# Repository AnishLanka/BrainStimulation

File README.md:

# BrainStimulation — Prototype Demo 2 / PCB Package Rev C

By Pythagoras Carayannopoulos, Peter Zhao and Anish Lanka.
Presentation: [`docs/Prototype_Demo_2.pdf`](docs/Prototype_Demo_2.pdf)

Start with `docs/RevC_Release/READ_ME_FIRST.txt` and `docs/RevC_Release/Integration_Guide.html`.
Upload each board's manufacturing ZIP to JLCPCB as a separate bare PCB design.
Do not upload the complete release archive as one PCB.

## TEAM

| Person | Responsibilities |
|--------|------------------|
| Pythagoras Carayannopoulos (Pyth) | Boost, Howland Pump circuit design, soldering, testing |
| Anish Lanka | Rail Splitter, Buck-Boost, Howland Pump schematic and PCB, soldering, testing |
| Peter Zhao | Signal Generator, firmware (ESP32-S3 controller, RP2040 DDS, web and Android apps), testing |

## SYSTEM OVERVIEW

The signal generator sets the shape of the stimulation current. The power path
provides the energy and voltage to push it. The two paths meet at the Howland,
which turns the voltage command into a current.

```
POWER PATH   Battery ──► Buck-Boost ──► Isolated 12 V ──► Boost ──► Rail Splitter
             2.8–3.7 V   steady 3.3 V   new isolated      79.7 V    ±39.85 V about MID
                                        domain                           │ ±40 V
                                                                         ▼
                                                                     Howland ──► External load
                                                                         ▲      electrodes; 2–5 kΩ on bench
                                                                         │ ±3.3 V command
SIGNAL PATH  Pico 2 W ──► ISOW7741 ──────► DAC8830 ──────► OPA2192
             samples      isolates SPI     code→0–3.3 V    bipolar ±3.3 V
                          and power
```

Compared with the Stim the Brim design we built on (~60 V boost, ±30 V rails),
ours uses ~80 V / ±40 V so firmware can limit output to ±30 V without clipping
from rail saturation.

## REPOSITORY LAYOUT

Every board folder follows the same pattern:

```
<Board>/
  *_JLCPCB.zip / *_fabrication.zip   Gerbers — upload this to JLCPCB
  Release_DRC.json                   Rev C release DRC report
  kicad/
    Anish_Work/                      Anish's KiCad files for this board
    Peter_Work/                      Peter's KiCad files for this board
    Pyth_Work/                       Pyth's KiCad files for this board
```

Open the `.kicad_pro` inside a `*_Work/` folder and keep that folder together —
project libraries are referenced relatively. Empty work folders hold a `.gitkeep`.

```
boards/
  Boost/                 Boost_79V7_Prototype_JLCPCB.zip, Boost_FINAL_ASSEMBLY_BOM.csv
    kicad/Pyth_Work/       Boost_Electrical_Draft.kicad_pro (Rev C project)
                           Boost_Convertor_Circuit_Pyth.kicad_sch (working changes)
  Buck_Boost/            BuckBoost_RevB_fabrication.zip
    kicad/Pyth_Work/       BuckBoost_RevB.kicad_pro (Rev C project)
                           BuckBoost_RevBPythWork.zip (working copy of project)
  Rail_Splitter/         RailSplitter_Prototype_JLCPCB.zip, RailSplitter_FINAL_ASSEMBLY_BOM.csv
    kicad/Anish_Work/      RailSplitter_Electrical_Draft.kicad_pro (Rev C project)
                           AmplifierCircuit_MYCHANGES.kicad_sch (working changes)
  Howland_Pump/          HowlandPump_JLCPCB.zip, Howland_Read_Only_Calculation.json
    kicad/Anish_Work/      HowlandPump-AnishWork.kicad_pro (current, Oct 2)
                           older_versions/ (FINAL + Backout, Sep 30)
  Signal_Generator/      SignalGen_Prototype_RevC_JLCPCB.zip, FIRMWARE_COMPATIBILITY.txt
    kicad/Peter_Work/      SignalGen_Electrical_Draft.kicad_pro (Rev C project)
  Shared/                Boards not assigned to a single owner
    Channel_ADC_Interface_RevC/   kicad/Peter_Work/Channel_ADC_Interface_RevC.kicad_pro
    Channel_Monitor_C1/           kicad/Peter_Work/Channel_Monitor_C1.kicad_pro
    Monitor_Power_C1/             kicad/Peter_Work/Monitor_Power_C1.kicad_pro
    Shared_Power_RevC/            kicad/Peter_Work/Shared_Power_Adapter_RevC.kicad_pro
docs/
  Prototype_Demo_2.pdf              Prototype Demo 2 presentation
  Firmware.md                       Firmware guide (commands, protocol, pins, build)
  RevC_Release/                     System-level release documents:
                                    READ_ME_FIRST.txt, Integration_Guide.html,
                                    Wiring_Map.json, Release_Checks.json, SHA256SUMS.json,
                                    Existing_Power_Review, Legacy_Power_Assembly/
firmware/                         Peter Zhao
  ESP32_S3_Brainstim_FW/            ESP32-S3 main controller (ESP-IDF 5.4): BLE control,
                                    4-channel FSM, OLED, battery/ADC; web/ BLE test UI;
                                    mobile/ Capacitor Android app; tests/ host simulations
  RP2040_DDS_FW/                    DDS daughter card, now Pico 2 W + DAC8830 (Pico SDK
                                    2.2.0; folder name is historical): DMA-paced SPI DAC
                                    streaming, waveform tables, I2C slave
releases/
  StimPrototype_Prototype_Package_RevC.zip   Original Rev C archive, unmodified
```

The files from the release archive have been distributed into the folders above.
Paths inside `Integration_Guide.html`, `Release_Checks.json` and `SHA256SUMS.json`
refer to the original archive layout — use the zip in `releases/` when you need
those links and checksums to line up.

## BOARDS AND TEST STATUS (Prototype Demo 2)

| Board | Owner | Soldered | Bench result |
|-------|-------|----------|--------------|
| Buck-Boost RevB | Anish | Yes | **Pass** — 3.3036 V out (target 3.3 V). Battery not yet on hand. |
| Boost 79.7 V | Pyth | Yes | **Pass** — 12 V in, ~79.5 V out (scope average). |
| Rail Splitter | Anish | Yes | **Open** — could not bring input to full voltage; op amp possibly damaged. Split appeared even. |
| Howland Pump | Pyth (design) / Anish (schematic + PCB) | Yes | **Fail** — measured 96 V peak-to-peak; LTspice simulation works. Not yet debugged. |
| Signal Generator RevC | Peter | Yes | Fixes applied (below); expected ±3.3 V output. |
| Monitor Power C1 | Shared | — | New in Rev C — one local supply per channel. |
| Channel Monitor C1 | Shared | — | New in Rev C — external sensing/relay board. |
| Channel ADC Interface RevC | Shared | — | New in Rev C — isolated simultaneous I/V sampler per channel. |
| Shared Power RevC | Shared | — | New in Rev C — OPTIONAL regulated 5 V bench adapter (not a raw-cell supply). |

## DESIGN NOTES

**Buck-Boost (TPS63001).** Steps the 2.8–3.7 V battery up or down to a steady
3.3 V. The battery starts near 3.7 V and decays toward 2.8 V.

**Boost (LM5155).** 12 V in → 79.7 V out. Vout = Vin ÷ (1 − D), so the switch is on
about 85 % of the time.
- Feedback set to 79.7 V: R1 = 787 kΩ, R2 = 10 kΩ.
- Parts that see 80 V were up-rated: Q1 100 V → 150 V; D1 100 V → 200 V;
  top feedback resistor 0603 (~75 V max) → 1206 (200 V);
  C5 22 µF / 100 V → 100 µF / 160 V.

**Rail Splitter (OPA455).** Splits 79.7 V into HV_TOP = +39.85 V,
MID = 0 V, HV_BOTTOM = −39.85 V (relative to MID). MID is the reference for the
Howland and the isolated signal stage. Matched 100 kΩ 0.1 % divider, output
resistor for stability, added bulk and rail-to-rail filter capacitors, and a
+40 / MID / −40 connector to other boards.

**Howland Pump (OPA462).** Circuit designed by Pyth; schematic and PCB by Anish. Designed for up to ±5 mA. Rails are ±40 V
rather than ±30 V to avoid saturation near the voltage limit. The 2 kΩ Rload1
placeholder is DNP; use external 2–5 kΩ dummy loads. A read-only calculation in
the release flags a resistor-ratio mismatch; the proposed R11 20k → 24k
correction is **not** applied. Confirm fitted values before wiring.

**Signal Generator (Pico 2 W → ISOW7741 → DAC8830 → OPA2192).**
Vout = 2 × Vdac − 3.3 V, so DAC 0 / 1.65 / 3.3 V → −3.3 / 0 / +3.3 V.
- The DAC8830 output (~6.25 kΩ source) was driving a 10 kΩ load directly;
  the OPA2192 now buffers it.
- Footprint changed from the 6-pin DAC8411 to the 8-pin DAC8830.
- At power-up the DAC outputs code 0 = −3.3 V (full negative). **Firmware must set
  mid-scale first.**
- Firmware is now modular: TypeScript front-end web app, C back-end, Student and
  Teacher views.

## FIRMWARE

Written by Peter Zhao.

Full documentation: [`docs/Firmware.md`](docs/Firmware.md) — architecture, BLE
commands, I2C protocol, pin maps, safety sequencing, build/test and TODOs.

Two projects that must be updated together — they share the 15-byte GET_STATUS v2
I2C protocol. Detailed handoff: `firmware/ESP32_S3_Brainstim_FW/docs/phase1.md`.
Keep both folders side by side: the host tests find the RP2040 code at
`../RP2040_DDS_FW`.

- **RP2040:** `cmake -S . -B build-phase1 -G Ninja -DCMAKE_BUILD_TYPE=Release`, then
  `cmake --build build-phase1` (needs `PICO_SDK_PATH`, `PICO_TOOLCHAIN_PATH`).
- **ESP32-S3:** `idf.py build` with ESP-IDF 5.4.
- **Host tests:** `node tests/run_phase1.mjs` from `ESP32_S3_Brainstim_FW/`
  (needs Node and Clang with wasm-ld).
- Build output (`build/`, `build-*/`, `sdkconfig.old`, `node_modules/`) is
  git-ignored. Regenerate locally.

Not yet flashed or validated on hardware. The ESP32 refuses stimulation until HV
GPIO assignments and polarity are confirmed in `main/gpio_pins.h`.

## ORDER SETTINGS

2 layers; FR4; nominal 0.4 mm; 1 oz copper; ENIG; green mask; white silk;
tented vias. Follow the per-board README. These files do not order assembled
PCBs or purchase components. Support these thin boards during assembly.

## CHECKS

`Release_Checks.json` in the release archive records a fresh DRC (KiCad 10.0.6,
2026-10-17) on every packaged native project; reports are in `Release_Validation/`
and file hashes in `SHA256SUMS.json`. DRC/ERC validate file connectivity and
geometry, not powered performance.

## OPEN ISSUES

1. Howland: 96 V p-p on the bench despite a working simulation — investigate.
2. Rail Splitter: replace/verify the op amp and retest at full 79.7 V input.
3. `boards/Rail_Splitter/kicad/Anish_Work/AmplifierCircuit_MYCHANGES.kicad_sch` lists C1–C4 as
   **10 V** capacitors, but they sit on an 80 V / ±40 V rail (the presented design
   uses 100 V parts). Check which values were actually fitted.
4. Battery, charger and protection not yet selected; runtime unknown.
5. Do not parallel separate 3.3 V outputs. The two primary supply connectors on
   each SignalGen board are internally tied together.
6. Firmware/hardware DAC mismatch — **resolved 2026-10-30**: the next build targets
   the **DAC8830 on a Pico 2 W**, and `firmware/RP2040_DDS_FW` was retargeted
   accordingly (16-bit mode-0 frames, PIO CS framing, Rev C pin map, EN/FLT fault
   bit). Still open: compile with the Pico SDK, re-run the host tests, scope the
   DAC interface, and decide how the board's second channel is driven
   (`boards/Signal_Generator/FIRMWARE_COMPATIBILITY.txt`, `docs/Firmware.md`).

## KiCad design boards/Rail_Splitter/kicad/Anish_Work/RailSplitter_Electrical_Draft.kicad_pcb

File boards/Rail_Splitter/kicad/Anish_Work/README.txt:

RAIL SPLITTER - ENGINEERING BENCH PROTOTYPE

Open RailSplitter_Electrical_Draft.kicad_pro in KiCad10. The schematic, PCB and local libraries
are included. The routed PCB matches the schematic and passes the checks in
PCB_DRC.json / PCB_Validation.json. Read PCB_Draft_Notes.txt for mechanics,
pinout and layout decisions, Draft_Review.txt for electrical assumptions, and
Fabrication_Order_Notes.txt for the0.4 mm bare-board order. The top-level upload
archive is RailSplitter_Prototype_JLCPCB.zip. The hardware still requires assembly and bench testing.

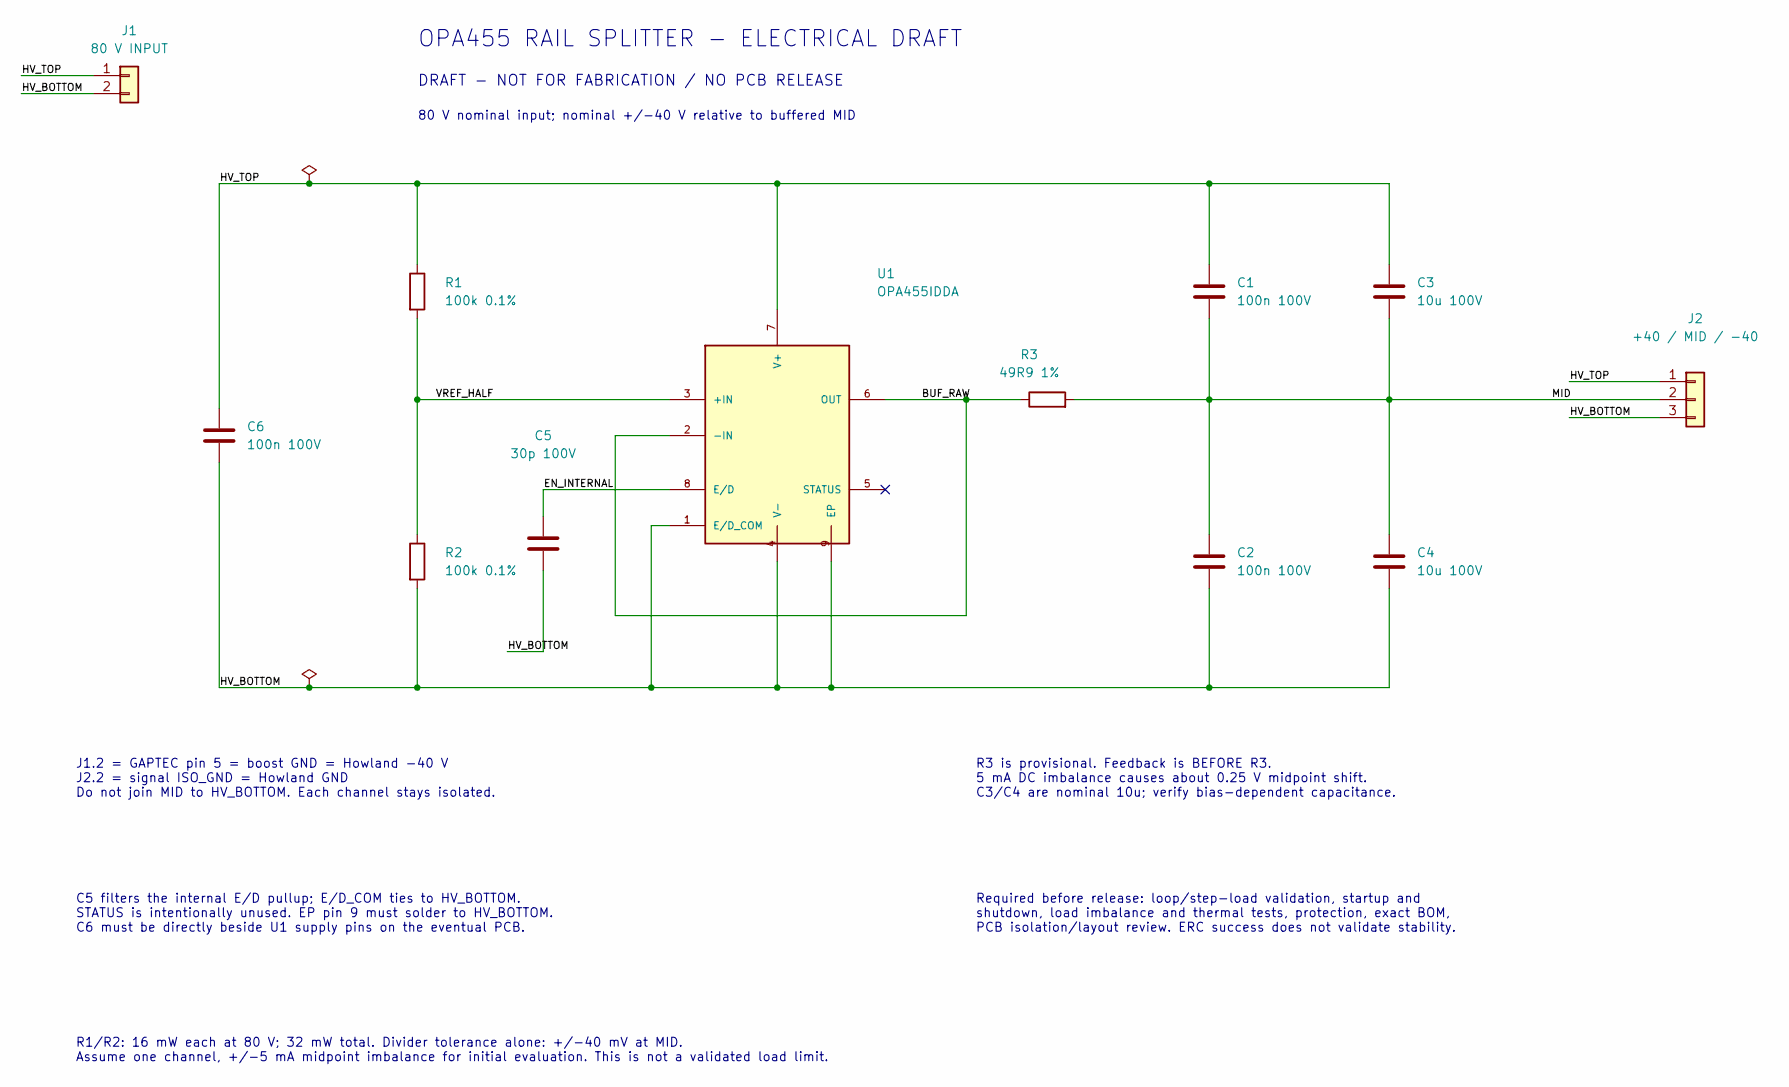
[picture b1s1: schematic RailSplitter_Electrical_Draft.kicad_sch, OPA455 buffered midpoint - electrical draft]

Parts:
C1, C2, C6: 100n 100V; C0805; MPN C2012X7R2A104K125AA
C3, C4: 10u 100V; C1210; MPN GRM32EC72A106KE05K
C5: 30p 100V; C0603
J1: 80 V INPUT; J2
J2: +40 / MID / -40; J3
R1, R2: 100k 0.1%; R0805; Rating 0.125W minimum; 100V minimum working vo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
R3: 49R9 1%; R0805; Rating 0.125W minimum
U1: OPA455IDDA; OPA455_DDA0008J; MPN OPA455IDDA

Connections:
/BUF_RAW: R3.1, U1.2 (-IN), U1.6 (OUT)
/EN_INTERNAL: C5.1, U1.8 (E/D)
/HV_BOTTOM: C2.2, C4.2, C5.2, C6.2, J1.2, J2.3, R2.2, U1.1 (E/D_COM), U1.4 (V-), U1.9 (EP)
/HV_TOP: C1.1, C3.1, C6.1, J1.1, J2.1, R1.1, U1.7 (V+)
/MID: C1.2, C2.1, C3.2, C4.1, J2.2, R3.2
/VREF_HALF: R1.2, R2.1, U1.3 (+IN)

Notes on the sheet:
OPA455 RAIL SPLITTER - ELECTRICAL DRAFT
DRAFT - NOT FOR FABRICATION / NO PCB RELEASE
80 V nominal input; nominal +/-40 V relative to buffered MID
J1.2 = GAPTEC pin 5 = boost GND = Howland -40 V J2.2 = signal ISO_GND = Howland GND Do not join MID to HV_BOTTOM. Each channel stays isolated.
R3 is provisional. Feedback is BEFORE R3. 5 mA DC imbalance causes about 0.25 V midpoint shift. C3/C4 are nominal 10u; verify bias-dependent capacitance.
C5 filters the internal E/D pullup; E/D_COM ties to HV_BOTTOM. STATUS is intentionally unused. EP pin 9 must solder to HV_BOTTOM. C6 must be directly beside U1 supply pins on the eventual PCB.
Required before release: loop/step-load validation, startup and shutdown, load imbalance and thermal tests, protection, exact BOM, PCB isolation/layout review. ERC success does not validate stability.
R1/R2: 16 mW each at 80 V; 32 mW total. Divider tolerance alone: +/-40 mV at MID. Assume one channel, +/-5 mA midpoint imbalance for initial evaluation. This is not a validated load limit.

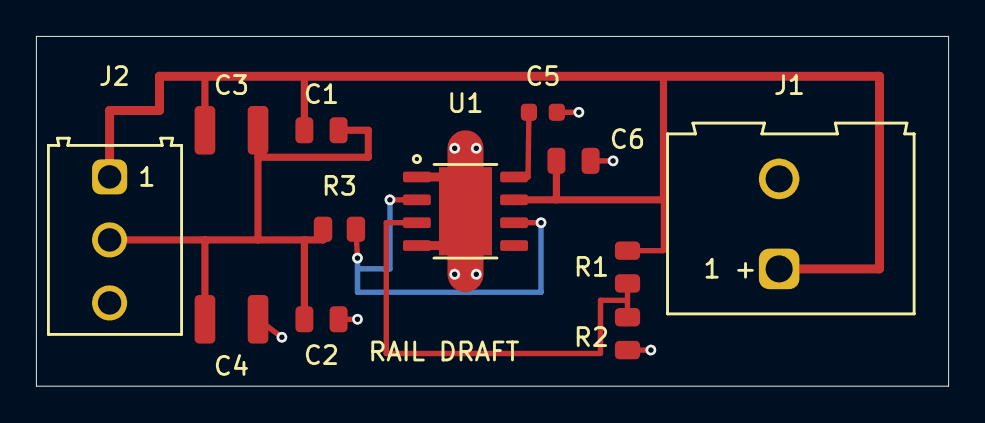
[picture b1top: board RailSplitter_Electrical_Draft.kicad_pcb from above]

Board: 2 copper layers, 50.7 x 19.4 mm, 12 parts (0 on the bottom side), 6 nets.

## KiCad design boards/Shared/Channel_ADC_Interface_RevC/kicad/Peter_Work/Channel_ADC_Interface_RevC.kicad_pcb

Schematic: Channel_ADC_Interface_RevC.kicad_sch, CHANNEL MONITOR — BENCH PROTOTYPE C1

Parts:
C201, C207: 1.2n; C_0805_2012Metric; MPN C0805C122F5GACTU
C202, C204, C208, C210: 1n; C_0805_2012Metric; MPN C0805C102F5GACTU
C203, C209: 6.8n; C_0805_2012Metric; MPN C0805C682F5GACTU
C205, C211: 8.2n; C_0805_2012Metric; MPN C0805C822F5GACTU
C206, C212, C219, C221, C223, C224, C225, C226, C227, C228: 100n; C_0805_2012Metric; MPN C0805C104K4RACTU
C213, C216, C220, C222: 22u; C_1210_3225Metric; MPN GRM32ER71C226KEA8L
J201: HOST_CONTROL_TELEMETRY; PinHeader_1x08_P2.54mm_Vertical; MPN TSW-108-07-G-S
J202: CORE_ADC_CONTROL_LINK; PinHeader_2x07_P2.54mm_Vertical; MPN TSW-107-07-G-D
R201, R202, R209, R210: 2k; R_0805_2012Metric; MPN TNPW08052K00BEEA
R203, R211: 470R; R_0805_2012Metric; MPN TNPW0805470RBEEA
R204, R212: 1.47k; R_0805_2012Metric; MPN TNPW08051K47BEEA
R205, R206, R213, R214: 604R; R_0805_2012Metric; MPN TNPW0805604RBEEA
R207, R208, R215, R216: 10R; R_0805_2012Metric; MPN TNPW080510R0BEEA
R221, R222, R223, R229, R230, R231, R232, R233, R234, R235, R236, R237: 10k; R_0805_2012Metric; MPN TNPW080510K0BEEA
R224, R225, R226, R227, R228: 33R; R_0805_2012Metric; MPN TNPW080533R0BEEA
R238, R239: 0.1R; R_0805_2012Metric; MPN WSL0805R1000FEA
U201, U202: OPA2320; SOIC-8_3.9x4.9mm_P1.27mm; MPN OPA2320AID
U204: ADS8353; TSSOP-16_4.4x5mm_P0.65mm; MPN ADS8353IPW
U205: ISO7741F; SOIC-16W_7.5x10.3mm_P1.27mm; MPN ISO7741FDWR
U206: ISO7721F; SOIC-16W_7.5x10.3mm_P1.27mm; MPN ISO7721FDWR
U207: Raspberry Pi Pico RP2040; RaspberryPi_Pico_Common_THT; MPN SC0915
U208: SN74LVC1G08; SOT-23-5; MPN SN74LVC1G08DBVR
U209: SN74LVC2G17; SOT-23-6; MPN SN74LVC2G17DBVR

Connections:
/ADC_CS_N: R221.2, R224.2, U204.11 (~CS)
/ADC_REF_A: R238.1, U204.3 (REFIO_A)
/ADC_REF_B: R239.1, U204.6 (REFIO_B)
/ADC_SCLK: R222.1, R225.2, U204.12 (SCLK)
/ADC_SDI: R223.1, R226.2, U204.10 (SDI)
/ADC_SDO_A: R227.1, U204.13 (SDO_A)
/ADC_SDO_B: R228.1, U204.14 (SDO_B)
/ARM_EDGE: J202.9, U205.13 (OUTB)
/FAULT_CLEAR_N: J202.11, R237.1, U205.11 (IND), U209.1 (1A)
/HEARTBEAT: J202.10, U205.12 (OUTC)
/HOST_3V3: C223.1, C225.1, J201.1, R234.2, U205.1 (VCC1), U205.7 (EN1), U206.3 (VCC1)
/HOST_ARM: J201.4, R230.1, U205.4 (INB)
/HOST_FAULT_OK: J201.6, R233.1, U205.6 (OUTD)
/HOST_GND: C223.2, C225.2, J201.2, R229.2, R230.2, R231.2, R233.2, U205.2 (GND1), U205.8 (GND1), U206.1 (GND1), U206.7 (GND1)
/HOST_HB: J201.5, R231.1, U205.5 (INC)
/HOST_RUN: J201.3, R229.1, U205.3 (INA)
/HOST_UART_RX: J201.8, U206.4 (OUTA)
/HOST_UART_TX: J201.7, R234.1, U206.5 (INB)
/INHIBITED: J202.12, U209.3 (2A)
/ISOLATED_HOST_RUN: R232.1, U205.14 (OUTA), U208.1 (A)
/I_ADC_N: C205.2, R208.2, U204.2 (AINM_A)
/I_ADC_P: C205.1, R207.2, U204.1 (AINP_A)
/I_F1A: C201.1, R203.2, R204.1
/I_F1B: C202.1, R204.2, U201.3 (INA+)
/I_F2A: C203.1, R205.2, R206.1
/I_F2B: C204.1, R206.2, U201.5 (INB+)
/I_HALF: R201.2, R202.1, R203.1
/I_LP1: C201.2, R205.1, U201.1 (OUTA), U201.2 (INA-)
/I_LP2: C203.2, R207.1, U201.6 (INB-), U201.7 (OUTB)
/I_MON: J202.5, R201.1
/LOCAL_READY: R236.1, U207.10 (GP7), U208.2 (B)
/MID_CH_GND: C202.2, C204.2, C206.2, C208.2, C210.2, C212.2, C213.2, C216.2, C219.2, C220.2, C221.2, C222.2, C224.2, C226.2, C227.2, C228.2, J202.2, J202.4, R202.2, R208.1, R210.2, R216.1, R222.2, R223.2, R232.2, R236.2, R237.2, U201.4 (V-), U202.4 (V-), U204.4 (REFGND_A), U204.5 (REFGND_B), U204.15 (GND), U205.9 (GND2), U205.15 (GND2), U206.9 (GND2), U206.16 (GND2), U207.3 (GND), U207.8 (GND), U207.13 (GND), U207.18 (GND), U207.23 (GND), U207.28 (GND), U207.33 (AGND), U207.38 (GND), U208.3 (GND), U209.2 (GND)
/P3V3_CH: C224.1, C227.1, J202.3, U205.10 (EN2), U205.16 (VCC2), U208.5 (VCC)
/P5_CH: C206.1, C212.1, C219.1, C220.1, J202.1, U201.8 (V+), U202.8 (V+), U204.16 (AVDD), U207.39 (VSYS)
/PICO_3V3: C221.1, C222.1, C226.1, C228.1, R221.1, R235.2, U204.9 (DVDD), U206.14 (VCC2), U207.36 (3V3_OUT), U209.5 (VCC)
/PICO_ADC_CS_N: R224.1, U207.4 (GP2)
/PICO_ADC_SCLK: R225.1, U207.5 (GP3)
/PICO_ADC_SDI: R226.1, U207.6 (GP4)
/PICO_ADC_SDO_A: R227.2, U207.7 (GP5)
/PICO_ADC_SDO_B: R228.2, U207.9 (GP6)
/PICO_FAULT_OK: U207.11 (GP8), U209.6 (1Y)
/PICO_INHIBITED: U207.12 (GP9), U209.4 (2Y)
/PICO_UART_RX: U206.12 (OUTB), U207.2 (GP1)
/PICO_UART_TX: R235.1, U206.13 (INA), U207.1 (GP0)
/REF_A_CAP: C213.1, R238.2
/REF_B_CAP: C216.1, R239.2
/RUN_REQUEST: J202.8, U208.4 (Y)
/V_ADC_N: C211.2, R216.2, U204.7 (AINM_B)
/V_ADC_P: C211.1, R215.2, U204.8 (AINP_B)
/V_F1A: C207.1, R211.2, R212.1
/V_F1B: C208.1, R212.2, U202.3 (INA+)
/V_F2A: C209.1, R213.2, R214.1
/V_F2B: C210.1, R214.2, U202.5 (INB+)
/V_HALF: R209.2, R210.1, R211.1
/V_LP1: C207.2, R213.1, U202.1 (OUTA), U202.2 (INA-)
/V_LP2: C209.2, R215.1, U202.6 (INB-), U202.7 (OUTB)
/V_MON: J202.6, R209.1

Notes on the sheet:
CHANNEL ADC / ISOLATED LOCAL SAMPLER — REV C DUMMY-LOAD BENCH PROTOTYPE
0.5 Hz–40 kHz measurement target. ADS8353 + matched analogue filters + local Pico PIO/DMA + isolated UART and controls.
MID_CH_GND = channel core MID_CH; isolated from HOST_GND. Never parallel PICO_3V3 regulator output with core P3V3_CH.
External supplies through J201/J202 (flags are source declarations, not regulators):
OPA2320AID
TNPW08052K00BEEA
TNPW0805470RBEEA
TNPW08051K47BEEA
C0805C122F5GACTU
C0805C102F5GACTU
TNPW0805604RBEEA
C0805C682F5GACTU
TNPW080510R0BEEA
C0805C822F5GACTU
C0805C104K4RACTU
GRM32ER71C226KEA8L
ADS8353IPW
TNPW080510K0BEEA
TNPW080533R0BEEA
ISO7741FDWR
ISO7721FDWR
SC0915
SN74LVC1G08DBVR
SN74LVC2G17DBVR
TSW-108-07-G-S
TSW-107-07-G-D
WSL0805R1000FEA

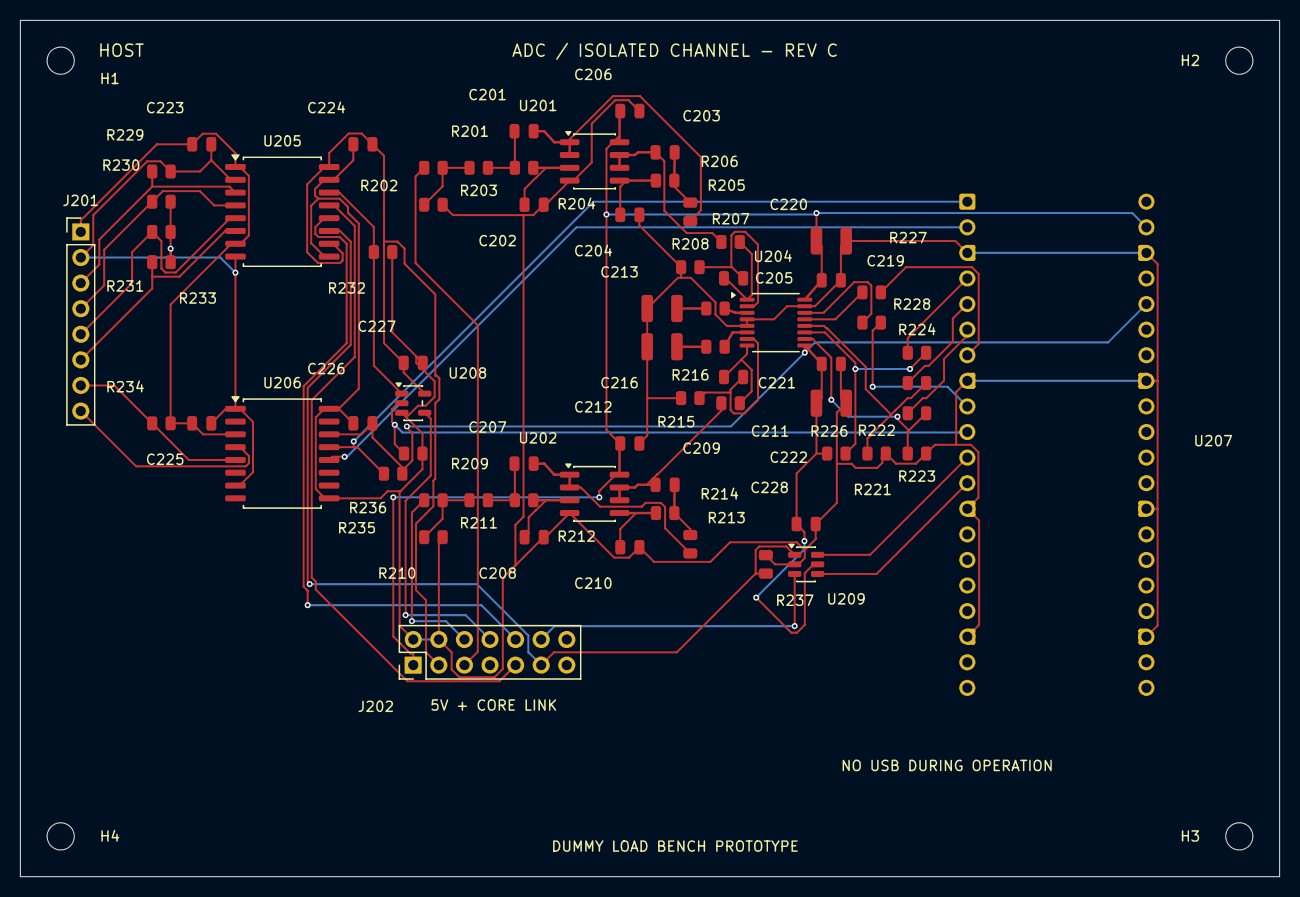
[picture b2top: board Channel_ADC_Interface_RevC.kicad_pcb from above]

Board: 2 copper layers, 125.0 x 85.0 mm, 73 parts (0 on the bottom side), 57 nets.

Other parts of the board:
H1, H2, H3, H4: M2.5 plastic support; MountingHole_2.7mm_M2.5

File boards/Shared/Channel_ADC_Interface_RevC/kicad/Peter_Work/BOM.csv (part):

Reference,Value,MPN,Footprint,Notes
U201,OPA2320,OPA2320AID,Package_SO:SOIC-8_3.9x4.9mm_P1.27mm,Matched two-stage unity-gain Sallen-Key low-pass. Second output drives ADC charge bucket through10R. SPICE/bench settling and phase margin remain required.
R201,2k,TNPW08052K00BEEA,Resistor_SMD:R_0805_2012Metric,Vishay TNPW0805 0.1% resistor. Ordering resistance uses R/K decimal notation; verify purchased reel against BOM.
R202,2k,TNPW08052K00BEEA,Resistor_SMD:R_0805_2012Metric,Vishay TNPW0805 0.1% resistor. Ordering resistance uses R/K decimal notation; verify purchased reel against BOM.
R203,470R,TNPW0805470RBEEA,Resistor_SMD:R_0805_2012Metric,Vishay TNPW0805 0.1% resistor. Ordering resistance uses R/K decimal notation; verify purchased reel against BOM.
R204,1.47k,TNPW08051K47BEEA,Resistor_SMD:R_0805_2012Metric,Vishay TNPW0805 0.1% resistor. Ordering resistance uses R/K decimal notation; verify purchased reel against BOM.
C201,1.2n,C0805C122F5GACTU,Capacitor_SMD:C_0805_2012Metric,"Feedback capacitor, C0G 1% candidate; match current and voltage channel parts."
C202,1n,C0805C102F5GACTU,Capacitor_SMD:C_0805_2012Metric,"Shunt capacitor, C0G 1% candidate; same lot recommended across I/V channels."
R205,604R,TNPW0805604RBEEA,Resistor_SMD:R_0805_2012Metric,Vishay TNPW0805 0.1% resistor. Ordering resistance uses R/K decimal notation; verify purchased reel against BOM.
R206,604R,TNPW0805604RBEEA,Resistor_SMD:R_0805_2012Metric,Vishay TNPW0805 0.1% resistor. Ordering resistance uses R/K decimal notation; verify purchased reel against BOM.
C203,6.8n,C0805C682F5GACTU,Capacitor_SMD:C_0805_2012Metric,"Feedback capacitor, C0G 1% candidate; match current and voltage channel parts."
C204,1n,C0805C102F5GACTU,Capacitor_SMD:C_0805_2012Metric,"Shunt capacitor, C0G 1% candidate; same lot recommended across I/V channels."
R207,10R,TNPW080510R0BEEA,Resistor_SMD:R_0805_2012Metric,Vishay TNPW0805 0.1% resistor. Ordering resistance uses R/K decimal notation; verify purchased reel against BOM.
R208,10R,TNPW080510R0BEEA,Resistor_SMD:R_0805_2012Metric,Vishay TNPW0805 0.1% resistor. Ordering resistance uses R/K decimal notation; verify purchased reel against BOM.
C205,8.2n,C0805C822F5GACTU,Capacitor_SMD:C_0805_2012Metric,"Differential ADC charge bucket, C0G 1%. Place at ADC pins. Not a substitute for the preceding anti-alias stages."
C206,100n,C0805C104K4RACTU,Capacitor_SMD:C_0805_2012Metric,"Local amplifier bypass, X7R16V candidate."
U202,OPA2320,OPA2320AID,Package_SO:SOIC-8_3.9x4.9mm_P1.27mm,Matched two-stage unity-gain Sallen-Key low-pass. Second output drives ADC charge bucket through10R. SPICE/bench settling and phase margin remain required.
R209,2k,TNPW08052K00BEEA,Resistor_SMD:R_0805_2012Metric,Vishay TNPW0805 0.1% resistor. Ordering resistance uses R/K decimal notation; verify purchased reel against BOM.
R210,2k,TNPW08052K00BEEA,Resistor_SMD:R_0805_2012Metric,Vishay TNPW0805 0.1% resistor. Ordering resistance uses R/K decimal notation; verify purchased reel against BOM.
R211,470R,TNPW0805470RBEEA,Resistor_SMD:R_0805_2012Metric,Vishay TNPW0805 0.1% resistor. Ordering resistance uses R/K decimal notation; verify purchased reel against BOM.
R212,1.47k,TNPW08051K47BEEA,Resistor_SMD:R_0805_2012Metric,Vishay TNPW0805 0.1% resistor. Ordering resistance uses R/K decimal notation; verify purchased reel against BOM.
C207,1.2n,C0805C122F5GACTU,Capacitor_SMD:C_0805_2012Metric,"Feedback capacitor, C0G 1% candidate; match current and voltage channel parts."
C208,1n,C0805C102F5GACTU,Capacitor_SMD:C_0805_2012Metric,"Shunt capacitor, C0G 1% candidate; same lot recommended across I/V channels."
R213,604R,TNPW0805604RBEEA,Resistor_SMD:R_0805_2012Metric,Vishay TNPW0805 0.1% resistor. Ordering resistance uses R/K decimal notation; verify purchased reel against BOM.
R214,604R,TNPW0805604RBEEA,Resistor_SMD:R_0805_2012Metric,Vishay TNPW0805 0.1% resistor. Ordering resistance uses R/K decimal notation; verify purchased reel against BOM.
C209,6.8n,C0805C682F5GACTU,Capacitor_SMD:C_0805_2012Metric,"Feedback capacitor, C0G 1% candidate; match current and voltage channel parts."
C210,1n,C0805C102F5GACTU,Capacitor_SMD:C_0805_2012Metric,"Shunt capacitor, C0G 1% candidate; same lot recommended across I/V channels."
R215,10R,TNPW080510R0BEEA,Resistor_SMD:R_0805_2012Metric,Vishay TNPW0805 0.1% resistor. Ordering resistance uses R/K decimal notation; verify purchased reel against BOM.
R216,10R,TNPW080510R0BEEA,Resistor_SMD:R_0805_2012Metric,Vishay TNPW0805 0.1% resistor. Ordering resistance uses R/K decimal notation; verify purchased reel against BOM.
C211,8.2n,C0805C822F5GACTU,Capacitor_SMD:C_0805_2012Metric,"Differential ADC charge bucket, C0G 1%. Place at ADC pins. Not a substitute for the preceding anti-alias stages."
C212,100n,C0805C104K4RACTU,Capacitor_SMD:C_0805_2012Metric,"Local amplifier bypass, X7R16V candidate."
C213,22u,GRM32ER71C226KEA8L,Capacitor_SMD:C_1210_3225Metric,22uF 16V X7R 1210 reservoir. Verify effective capacitance at 2.5V remains >=10uF; manufacturer DC bias curve governs. Internal reference only: no external driver.
C216,22u,GRM32ER71C226KEA8L,Capacitor_SMD:C_1210_3225Metric,22uF 16V X7R 1210 reservoir. Verify effective capacitance at 2.5V remains >=10uF; manufacturer DC bias curve governs. Internal reference only: no external driver.
U204,ADS8353,ADS8353IPW,Package_SO:TSSOP-16_4.4x5mm_P0.65mm,"32-clock dual-SDO, INTERNAL 2.5V references, single-ended 0..2.5V, straight binary. Firmware writes CFR=0x8040 and reads back before readiness. Default references are OFF: no valid data until configured and settled. Do not select 2x range. Both channels sample simultaneously."
C219,100n,C0805C104K4RACTU,Capacitor_SMD:C_0805_2012Metric,ADCAVDD bypass at pin16
C220,22u,GRM32ER71C226KEA8L,Capacitor_SMD:C_1210_3225Metric,AVDD reservoir: verify at least10u effective at5V per ADS8353 layout guideline.
C221,100n,C0805C104K4RACTU,Capacitor_SMD:C_0805_2012Metric,ADCDVDD bypass at pin9
C222,22u,GRM32ER71C226KEA8L,Capacitor_SMD:C_1210_3225Metric,DVDD reservoir: verify at least10u effective at3.3V per ADS8353 layout guideline.
R221,10k,TNPW080510K0BEEA,Resistor_SMD:R_0805_2012Metric,Vishay TNPW0805 0.1% resistor. Ordering resistance uses R/K decimal notation; verify purchased reel against BOM.
R222,10k,TNPW080510K0BEEA,Resistor_SMD:R_0805_2012Metric,Vishay TNPW0805 0.1% resistor. Ordering resistance uses R/K decimal notation; verify purchased reel against BOM.
R223,10k,TNPW080510K0BEEA,Resistor_SMD:R_0805_2012Metric,Vishay TNPW0805 0.1% resistor. Ordering resistance uses R/K decimal notation; verify purchased reel against BOM.
R224,33R,TNPW080533R0BEEA,Resistor_SMD:R_0805_2012Metric,Vishay TNPW0805 0.1% resistor. Ordering resistance uses R/K decimal notation; verify purchased reel against BOM.
R225,33R,TNPW080533R0BEEA,Resistor_SMD:R_0805_2012Metric,Vishay TNPW0805 0.1% resistor. Ordering resistance uses R/K decimal notation; verify purchased reel against BOM.
R226,33R,TNPW080533R0BEEA,Resistor_SMD:R_0805_2012Metric,Vishay TNPW0805 0.1% resistor. Ordering resistance uses R/K decimal notation; verify purchased reel against BOM.
R227,33R,TNPW080533R0BEEA,Resistor_SMD:R_0805_2012Metric,Vishay TNPW0805 0.1% resistor. Ordering resistance uses R/K decimal notation; verify purchased reel against BOM.
R228,33R,TNPW080533R0BEEA,Resistor_SMD:R_0805_2012Metric,Vishay TNPW0805 0.1% resistor. Ordering resistance uses R/K decimal notation; verify purchased reel against BOM.
U205,ISO7741F,ISO7741FDWR,Package_SO:SOIC-16W_7.5x10.3mm_P1.27mm,"F suffix defaults outputs LOW on input-side power loss. Side1 host, side2 single channel. FAULT_CLEAR_N high means recovered fault chain, not armed. Missing channel power returns low fault status. Isolation barrier layout and assembled leakage require validation."
R229,10k,TNPW080510K0BEEA,Resistor_SMD:R_0805_2012Metric,Vishay TNPW0805 0.1% resistor. Ordering resistance uses R/K decimal notation; verify purchased reel against BOM.
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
